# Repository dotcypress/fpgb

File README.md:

# Forth Programmable Breadboard

🚧 Work in progress. Don't try this at home. 🚧

## Resources

- [Firmware](firmware/)
- [Schematics](docs/fpgb.pdf)
- [PCB(KiCad project)](pcb/)
- [Gerber files](docs/gerber)

## License

Licensed under either of

- Apache License, Version 2.0 ([LICENSE-APACHE](LICENSE-APACHE) or
  http://www.apache.org/licenses/LICENSE-2.0)
- MIT license ([LICENSE-MIT](LICENSE-MIT) or http://opensource.org/licenses/MIT)

at your option.

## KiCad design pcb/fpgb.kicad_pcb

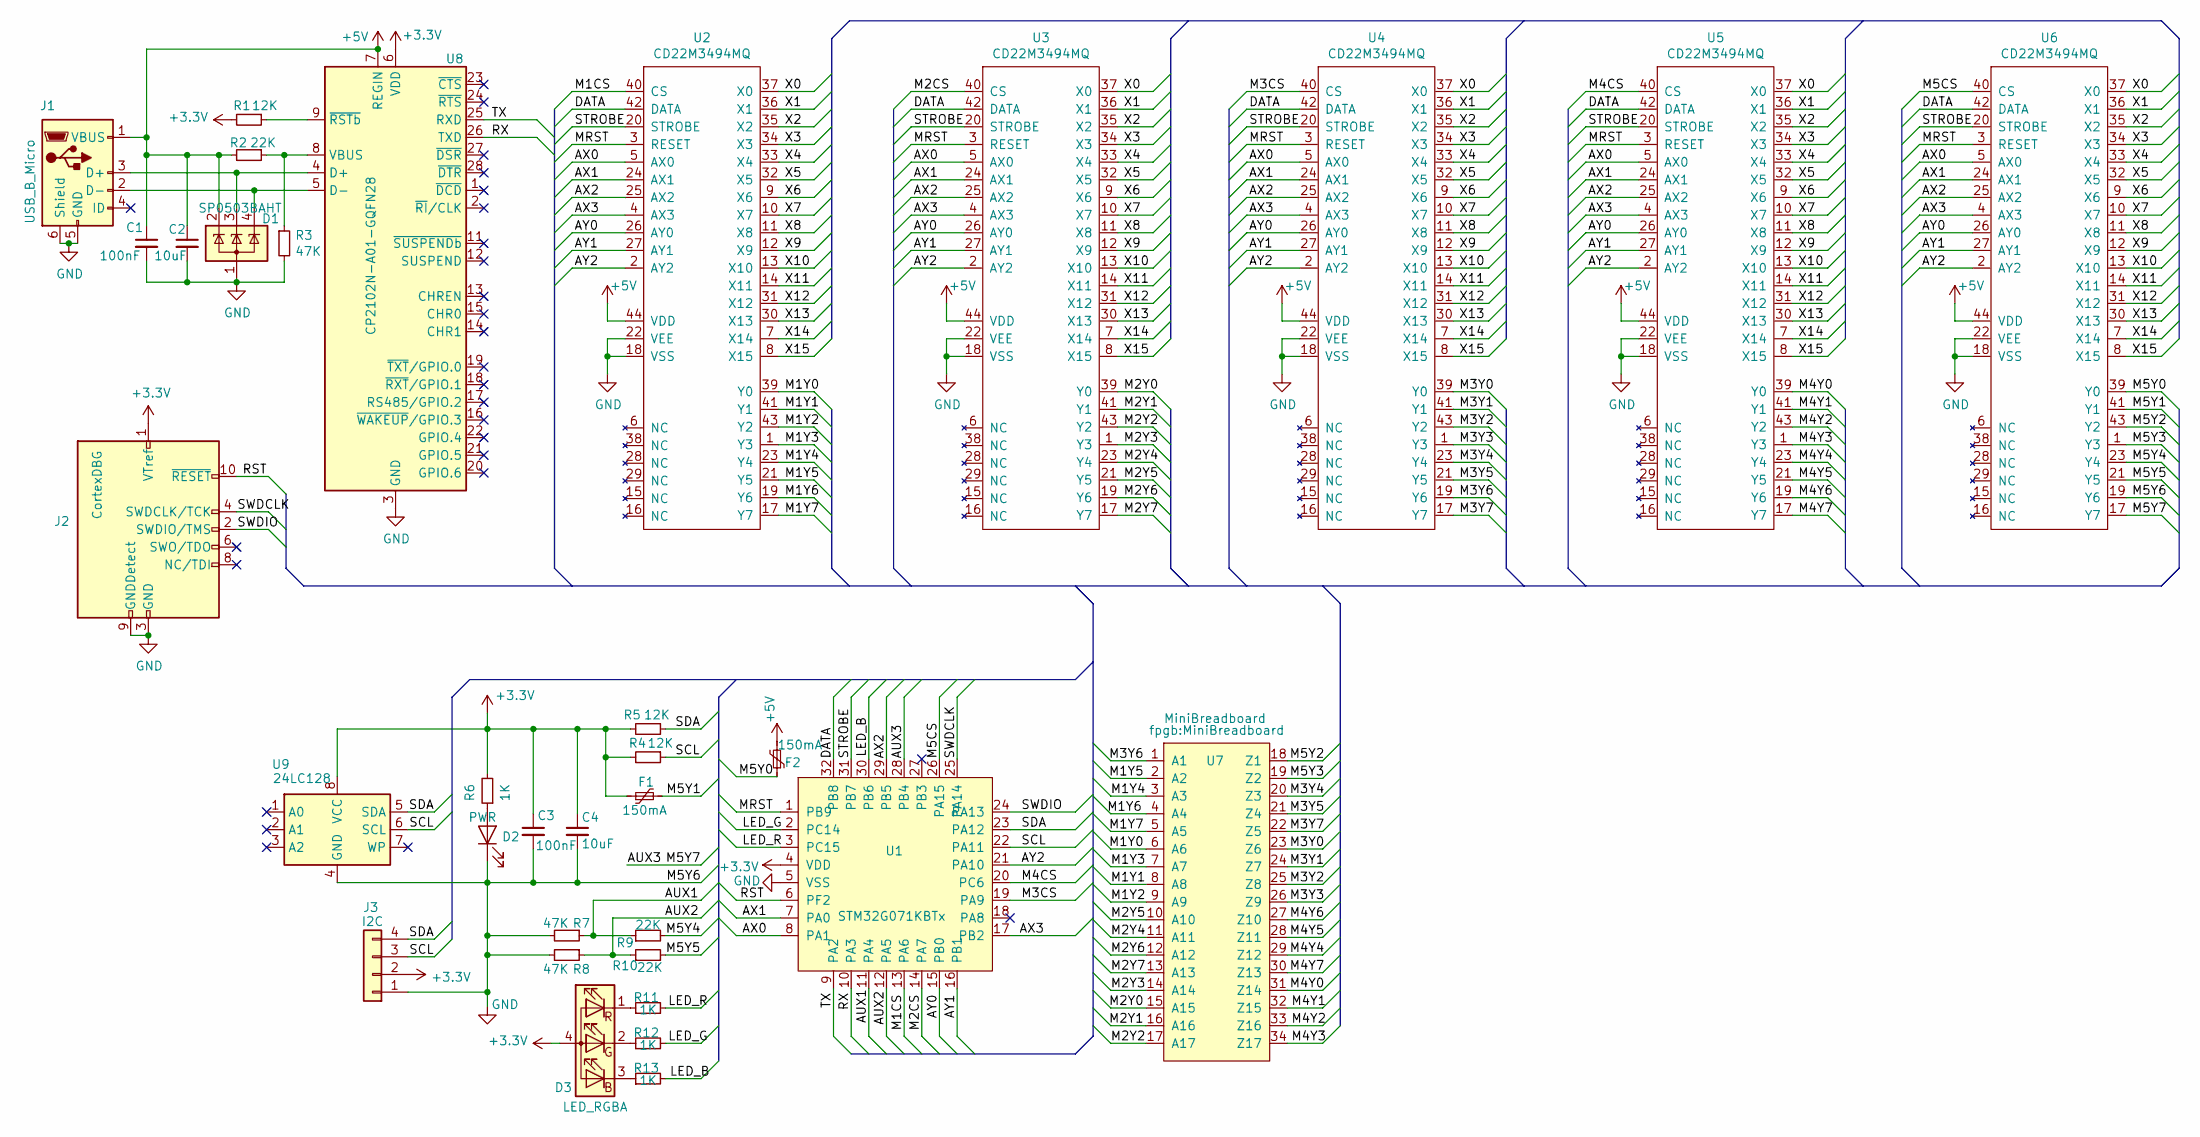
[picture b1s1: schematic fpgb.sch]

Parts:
C1, C3: 100nF; C_0603_1608Metric
C2, C4: 10uF; C_0603_1608Metric
D1: SP0503BAHT; SOT-143
D2: PWR; LED_0603_1608Metric
D3: LED_RGBA; LED_RGB_0606
F1, F2: 150mA; Fuse_1206_3216Metric
J1: USB_B_Micro; USB_Micro-B_Amphenol_10103594-0001LF_Horizontal
J2: CortexDBG; PinHeader_2x05_P1.27mm_Vertical_SMD
J3: I2C; PinSocket_1x04_P2.54mm_Vertical
R1, R4, R5: 12K; R_0603_1608Metric
R2, R9, R10: 22K; R_0603_1608Metric
R3, R7, R8: 47K; R_0603_1608Metric
R6, R11, R12, R13: 1K; R_0603_1608Metric
U1: STM32G071KBTx; LQFP-32_7x7mm_P0.8mm
U2, U3, U4, U5, U6: CD22M3494MQ; PLCC-44_16.6x16.6mm_P1.27mm
U7: MiniBreadboard
U8: CP2102N-A01-GQFN28; QFN-28-1EP_5x5mm_P0.5mm_EP3.35x3.35mm
U9: 24LC128; SOIC-8-1EP_3.9x4.9mm_P1.27mm_EP2.514x3.2mm

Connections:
+3V3: C3.1, C4.1, D3.4 (A), F1.1, J2.1 (VTref), J3.2, R1.2, R4.2, R5.2, R6.2, U1.4 (VDD), U8.6 (VDD), U9.8 (VCC)
+5V: C1.1, C2.1, D1.2 (K), F2.2, J1.1 (VBUS), R2.2, U2.44 (VDD), U3.44 (VDD), U4.44 (VDD), U5.44 (VDD), U6.44 (VDD), U8.7 (REGIN)
/AUX1: R7.1, R9.1, U1.11 (PA4)
/AUX2: R8.1, R10.1, U1.12 (PA5)
/AUX3: U1.28 (PB4), U6.17 (Y7)
/AX0: U1.8 (PA1), U2.5 (AX0), U3.5 (AX0), U4.5 (AX0), U5.5 (AX0), U6.5 (AX0)
/AX1: U1.7 (PA0), U2.24 (AX1), U3.24 (AX1), U4.24 (AX1), U5.24 (AX1), U6.24 (AX1)
/AX2: U1.29 (PB5), U2.25 (AX2), U3.25 (AX2), U4.25 (AX2), U5.25 (AX2), U6.25 (AX2)
/AX3: U1.17 (PB2), U2.4 (AX3), U3.4 (AX3), U4.4 (AX3), U5.4 (AX3), U6.4 (AX3)
/AY0: U1.15 (PB0), U2.26 (AY0), U3.26 (AY0), U4.26 (AY0), U5.26 (AY0), U6.26 (AY0)
/AY1: U1.16 (PB1), U2.27 (AY1), U3.27 (AY1), U4.27 (AY1), U5.27 (AY1), U6.27 (AY1)
/AY2: U1.21 (PA10), U2.2 (AY2), U3.2 (AY2), U4.2 (AY2), U5.2 (AY2), U6.2 (AY2)
/DATA: U1.32 (PB8), U2.42 (DATA), U3.42 (DATA), U4.42 (DATA), U5.42 (DATA), U6.42 (DATA)
/LED_B: R13.2, U1.30 (PB6)
/LED_G: R12.2, U1.2 (PC14)
/LED_R: R11.2, U1.3 (PC15)
/M1CS: U1.13 (PA6), U2.40 (CS)
/M1Y0: U2.39 (Y0), U7.6 (A6)
/M1Y1: U2.41 (Y1), U7.8 (A8)
/M1Y2: U2.43 (Y2), U7.9 (A9)
/M1Y3: U2.1 (Y3), U7.7 (A7)
/M1Y4: U2.23 (Y4), U7.3 (A3)
/M1Y5: U2.21 (Y5), U7.2 (A2)
/M1Y6: U2.19 (Y6), U7.4 (A4)
/M1Y7: U2.17 (Y7), U7.5 (A5)
/M2CS: U1.14 (PA7), U3.40 (CS)
/M2Y0: U3.39 (Y0), U7.15 (A15)
/M2Y1: U3.41 (Y1), U7.16 (A16)
/M2Y2: U3.43 (Y2), U7.17 (A17)
/M2Y3: U3.1 (Y3), U7.14 (A14)
/M2Y4: U3.23 (Y4), U7.11 (A11)
/M2Y5: U3.21 (Y5), U7.10 (A10)
/M2Y6: U3.19 (Y6), U7.12 (A12)
/M2Y7: U3.17 (Y7), U7.13 (A13)
/M3CS: U1.19 (PA9), U4.40 (CS)
/M3Y0: U4.39 (Y0), U7.23 (Z6)
/M3Y1: U4.41 (Y1), U7.24 (Z7)
/M3Y2: U4.43 (Y2), U7.25 (Z8)
/M3Y3: U4.1 (Y3), U7.26 (Z9)
/M3Y4: U4.23 (Y4), U7.20 (Z3)
/M3Y5: U4.21 (Y5), U7.21 (Z4)
/M3Y6: U4.19 (Y6), U7.1 (A1)
/M3Y7: U4.17 (Y7), U7.22 (Z5)
/M4CS: U1.20 (PC6), U5.40 (CS)
/M4Y0: U5.39 (Y0), U7.31 (Z14)
/M4Y1: U5.41 (Y1), U7.32 (Z15)
/M4Y2: U5.43 (Y2), U7.33 (Z16)
/M4Y3: U5.1 (Y3), U7.34 (Z17)
/M4Y4: U5.23 (Y4), U7.29 (Z12)
/M4Y5: U5.21 (Y5), U7.28 (Z11)
/M4Y6: U5.19 (Y6), U7.27 (Z10)
/M4Y7: U5.17 (Y7), U7.30 (Z13)
/M5CS: U1.26 (PA15), U6.40 (CS)
/M5Y0: F2.1, U6.39 (Y0)
/M5Y1: F1.2, U6.41 (Y1)
/M5Y2: U6.43 (Y2), U7.18 (Z1)
/M5Y3: U6.1 (Y3), U7.19 (Z2)
/M5Y4: R9.2, U6.23 (Y4)
/M5Y5: R10.2, U6.21 (Y5)
/MRST: U1.1 (PB9), U2.3 (RESET), U3.3 (RESET), U4.3 (RESET), U5.3 (RESET), U6.3 (RESET)
/RST: J2.10 (~RESET~), U1.6 (PF2)
/RX: U1.10 (PA3), U8.26 (TXD)
/SCL: J3.3, R4.1, U1.22 (PA11), U9.6 (SCL)
/SDA: J3.4, R5.1, U1.23 (PA12), U9.5 (SDA)
/STROBE: U1.31 (PB7), U2.20 (STROBE), U3.20 (STROBE), U4.20 (STROBE), U5.20 (STROBE), U6.20 (STROBE)
/SWDCLK: J2.4 (SWDCLK/TCK), U1.25 (PA14)
/SWDIO: J2.2 (SWDIO/TMS), U1.24 (PA13)
/TX: U1.9 (PA2), U8.25 (RXD)
/X0: U2.37 (X0), U3.37 (X0), U4.37 (X0), U5.37 (X0), U6.37 (X0)
/X1: U2.36 (X1), U3.36 (X1), U4.36 (X1), U5.36 (X1), U6.36 (X1)
/X2: U2.35 (X2), U3.35 (X2), U4.35 (X2), U5.35 (X2), U6.35 (X2)
/X3: U2.34 (X3), U3.34 (X3), U4.34 (X3), U5.34 (X3), U6.34 (X3)
/X4: U2.33 (X4), U3.33 (X4), U4.33 (X4), U5.33 (X4), U6.33 (X4)
/X5: U2.32 (X5), U3.32 (X5), U4.32 (X5), U5.32 (X5), U6.32 (X5)
/X6: U2.9 (X6), U3.9 (X6), U4.9 (X6), U5.9 (X6), U6.9 (X6)
/X7: U2.10 (X7), U3.10 (X7), U4.10 (X7), U5.10 (X7), U6.10 (X7)
/X8: U2.11 (X8), U3.11 (X8), U4.11 (X8), U5.11 (X8), U6.11 (X8)
/X9: U2.12 (X9), U3.12 (X9), U4.12 (X9), U5.12 (X9), U6.12 (X9)
/X10: U2.13 (X10), U3.13 (X10), U4.13 (X10), U5.13 (X10), U6.13 (X10)
/X11: U2.14 (X11), U3.14 (X11), U4.14 (X11), U5.14 (X11), U6.14 (X11)
/X12: U2.31 (X12), U3.31 (X12), U4.31 (X12), U5.31 (X12), U6.31 (X12)
/X13: U2.30 (X13), U3.30 (X13), U4.30 (X13), U5.30 (X13), U6.30 (X13)
/X14: U2.7 (X14), U3.7 (X14), U4.7 (X14), U5.7 (X14), U6.7 (X14)
/X15: U2.8 (X15), U3.8 (X15), U4.8 (X15), U5.8 (X15), U6.8 (X15)
GND: C1.2, C2.2, C3.2, C4.2, D1.1 (A), D2.1 (K), J1.5 (GND), J1.6 (Shield), J2.3 (GND), J2.5 (GND), J2.9 (GNDDetect), J3.1, R3.2, R7.2, R8.2, U1.5 (VSS), U2.18 (VSS), U2.22 (VEE), U3.18 (VSS), U3.22 (VEE), U4.18 (VSS), U4.22 (VEE), U5.18 (VSS), U5.22 (VEE), U6.18 (VSS), U6.19 (Y6), U6.22 (VEE), U8.3 (GND), U8.29 (GND), U9.4 (GND)
unnamed: D1.3 (K), J1.3 (D+), U8.4 (D+)
unnamed: D1.4 (K), J1.2 (D-), U8.5 (D-)
unnamed: D2.2 (A), R6.1
unnamed: D3.1 (RK), R11.1
unnamed: D3.2 (GK), R12.1
unnamed: D3.3 (BK), R13.1
unnamed: R1.1, U8.9 (~RSTb)
unnamed: R2.1, R3.1, U8.8 (VBUS)

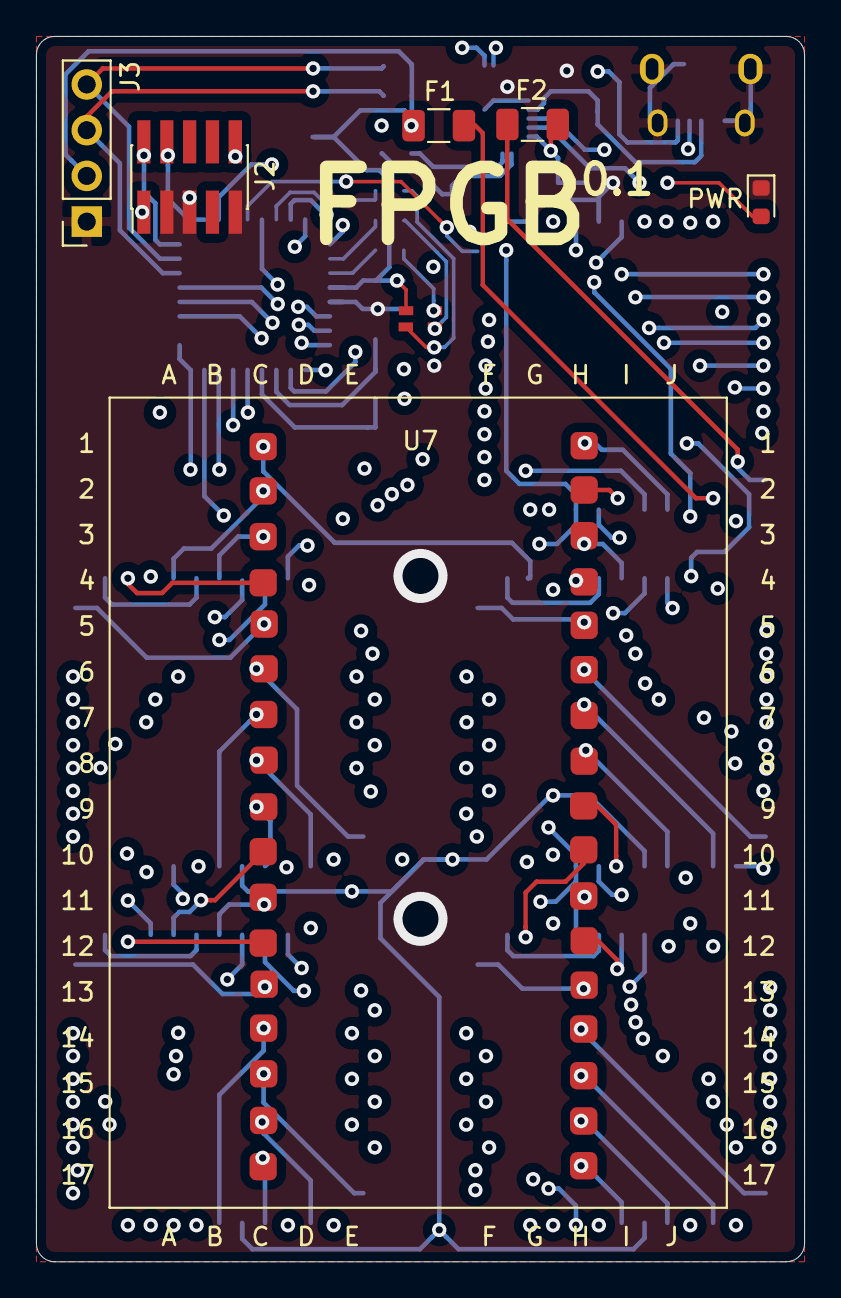
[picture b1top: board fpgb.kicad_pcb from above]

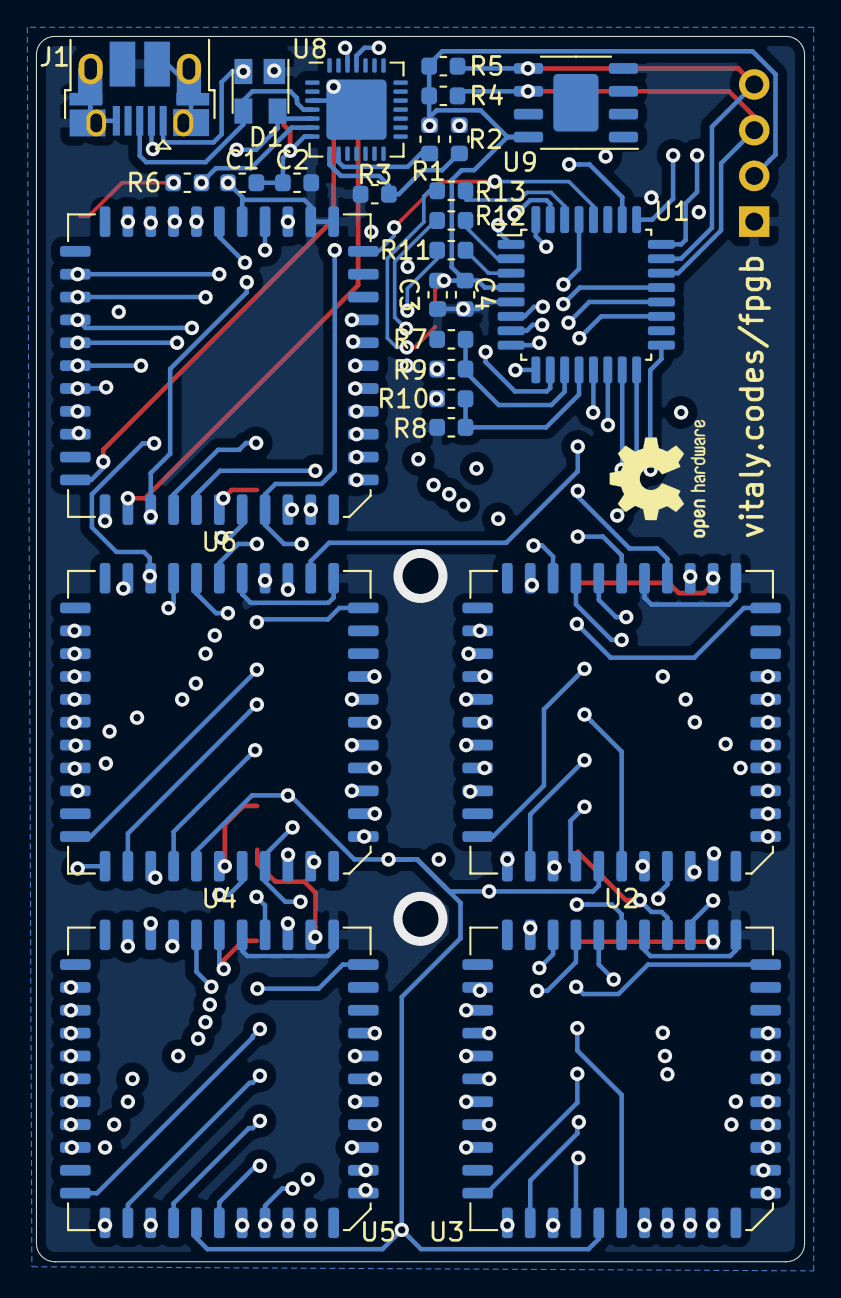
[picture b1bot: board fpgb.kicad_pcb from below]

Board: 4 copper layers, 42.7 x 68.1 mm, 34 parts (27 on the bottom side), 93 nets.

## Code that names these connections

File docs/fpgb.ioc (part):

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Mcu.Name=STM32G071K(6-8-B)Tx
Mcu.Package=LQFP32
Mcu.UserName=STM32G071KBTx
PA0.GPIOParameters=GPIO_Label
PA0.GPIO_Label=AX1
PA0.Signal=GPIO_Output
PA1.GPIOParameters=GPIO_Label
PA1.GPIO_Label=AX0
PA1.Signal=GPIO_Output
PA10.GPIOParameters=GPIO_Label
PA10.GPIO_Label=AY2
PA10.Signal=GPIO_Output
PA11\ [PA9].Mode=I2C
PA11\ [PA9].Signal=I2C2_SCL
PA12\ [PA10].Mode=I2C
PA12\ [PA10].Signal=I2C2_SDA
PA13.Mode=Serial_Wire
PA13.Signal=SYS_SWDIO
PA14-BOOT0.Mode=Serial_Wire
PA14-BOOT0.Signal=SYS_SWCLK
PA15.GPIOParameters=GPIO_Label
PA15.GPIO_Label=M5CS
PA15.Signal=GPIO_Output
PA2.Mode=Asynchronous
PA2.Signal=USART2_TX
PA3.Mode=Asynchronous
PA3.Signal=USART2_RX
PA4.Signal=COMP_DAC11_group
PA5.Mode=IN5
PA5.Signal=ADC1_IN5
PA6.GPIOParameters=GPIO_Label
PA6.GPIO_Label=M1CS
PA6.Signal=GPIO_Output
PA7.GPIOParameters=GPIO_Label
PA7.GPIO_Label=M2CS
PA7.Signal=GPIO_Output
PA9.GPIOParameters=GPIO_Label
PA9.GPIO_Label=M3CS
PA9.Signal=GPIO_Output
PB0.GPIOParameters=GPIO_Label
PB0.GPIO_Label=AY0
PB0.Signal=GPIO_Output
PB1.GPIOParameters=GPIO_Label
PB1.GPIO_Label=AY1
PB1.Signal=GPIO_Output
PB2.GPIOParameters=GPIO_Label
PB2.GPIO_Label=AX3
PB2.Signal=GPIO_Output
PB3.GPIOParameters=GPIO_Label
PB3.GPIO_Label=AUX3
PB3.Signal=GPIO_Output
PB5.GPIOParameters=GPIO_Label
PB5.GPIO_Label=AX2
PB5.Signal=GPIO_Output
PB6.GPIOParameters=GPIO_Label
PB6.GPIO_Label=LED_B
PB6.Signal=GPIO_Output
PB7.GPIOParameters=GPIO_Label
PB7.GPIO_Label=STROBE
PB7.Signal=GPIO_Output
PB8.GPIOParameters=GPIO_Label
PB8.GPIO_Label=DATA
PB8.Signal=GPIO_Output
PB9.GPIOParameters=GPIO_Label
PB9.GPIO_Label=MRST
PB9.Signal=GPIO_Output
PC14-OSC32_IN\ (PC14).GPIOParameters=GPIO_Label
PC14-OSC32_IN\ (PC14).GPIO_Label=LED_G
PC14-OSC32_IN\ (PC14).Signal=GPIO_Output
PC15-OSC32_OUT\ (PC15).GPIOParameters=GPIO_Label
PC15-OSC32_OUT\ (PC15).GPIO_Label=LED_R
PC15-OSC32_OUT\ (PC15).Signal=GPIO_Output
PC6.GPIOParameters=GPIO_Label
PC6.GPIO_Label=M4CS
PC6.Signal=GPIO_Output
PF2\ -\ NRST.GPIOParameters=GPIO_Label
PF2\ -\ NRST.GPIO_Label=RESET
PF2\ -\ NRST.Signal=GPIO_Input
RCC.HSE_VALUE=8000000
RCC.SYSCLKFreq_VALUE=16000000
board=custom

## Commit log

2020-03-08 prototype
2020-03-18 boot script support
2020-03-19 shell refactoring
2020-03-19 nets & ports
2020-05-24 update uart speed
2022-06-06 Bump linked-hash-map from 0.5.2 to 0.5.4 in /app
    Bumps [linked-hash-map](https://github.com/contain-rs/linked-hash-map) from 0.5.2 to 0.5.4.
    - [Release notes](https://github.com/contain-rs/linked-hash-map/releases)
    - [Commits](https://github.com/contain-rs/linked-hash-map/commits)
    ---
    updated-dependencies:
    - dependency-name: linked-hash-map
2022-06-06 Bump socket2 from 0.3.11 to 0.3.19 in /app
    Bumps [socket2](https://github.com/rust-lang/socket2) from 0.3.11 to 0.3.19.
    - [Release notes](https://github.com/rust-lang/socket2/releases)
    - [Changelog](https://github.com/rust-lang/socket2/blob/master/CHANGELOG.md)
    - [Commits](https://github.com/rust-lang/socket2/compare/0.3.11...v0.3.19)
    ---
    updated-dependencies:
2022-06-08 Bump miow from 0.2.1 to 0.2.2 in /app
    Bumps [miow](https://github.com/yoshuawuyts/miow) from 0.2.1 to 0.2.2.
    - [Release notes](https://github.com/yoshuawuyts/miow/releases)
    - [Changelog](https://github.com/yoshuawuyts/miow/blob/master/CHANGELOG.md)
    - [Commits](https://github.com/yoshuawuyts/miow/compare/0.2.1...0.2.2)
    ---
    updated-dependencies:
2022-06-15 Bump net2 from 0.2.33 to 0.2.37 in /app
    Bumps [net2](https://github.com/deprecrated/net2-rs) from 0.2.33 to 0.2.37.
    - [Release notes](https://github.com/deprecrated/net2-rs/releases)
    - [Commits](https://github.com/deprecrated/net2-rs/compare/0.2.33...0.2.37)
    ---
    updated-dependencies:
    - dependency-name: net2
2022-06-16 Bump arc-swap from 0.4.4 to 0.4.8 in /app
    Bumps [arc-swap](https://github.com/vorner/arc-swap) from 0.4.4 to 0.4.8.
    - [Release notes](https://github.com/vorner/arc-swap/releases)
    - [Changelog](https://github.com/vorner/arc-swap/blob/v0.4.8/CHANGELOG.md)
    - [Commits](https://github.com/vorner/arc-swap/compare/v0.4.4...v0.4.8)
    ---
    updated-dependencies:
2022-06-17 Bump smallvec from 0.6.13 to 0.6.14 in /app
    Bumps [smallvec](https://github.com/servo/rust-smallvec) from 0.6.13 to 0.6.14.
    - [Release notes](https://github.com/servo/rust-smallvec/releases)
    - [Commits](https://github.com/servo/rust-smallvec/compare/v0.6.13...v0.6.14)
    ---
    updated-dependencies:
    - dependency-name: smallvec
2022-06-17 Bump thread_local from 1.0.1 to 1.1.4 in /app
    Bumps [thread_local](https://github.com/Amanieu/thread_local-rs) from 1.0.1 to 1.1.4.
    - [Release notes](https://github.com/Amanieu/thread_local-rs/releases)
    - [Commits](https://github.com/Amanieu/thread_local-rs/compare/v1.0.1...1.1.4)
    ---
    updated-dependencies:
    - dependency-name: thread_local
2023-06-14 Bump net2 from 0.2.33 to 0.2.38 in /app
    Bumps [net2](https://github.com/deprecrated/net2-rs) from 0.2.33 to 0.2.38.
    - [Commits](https://github.com/deprecrated/net2-rs/compare/0.2.33...0.2.38)
    ---
    updated-dependencies:
    - dependency-name: net2
    dependency-type: indirect
